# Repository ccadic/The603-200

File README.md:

# The603-200
A modern opensource watch in a vintage shell
https://hackaday.io/project/181159-the-603-200-watch
©2021 – Morpheans.com – pcadic@gmail.com 

**Description of the product**
The 603-200 is the first watch of a planed line of watches based on the same concept which is inspired by the Japanese TokyoFlash® brand (www.tokyoflash.com). We want to push the concept to a fully modern connected watch capable of establishing communication with your SmartPhone or any other IoT.
This watch is an open source device. The customers and makers have access to all the documentation

  •	Kicad-Pcb® files to make correction or updates
  •	Arduino IDE Sketches available from www.github.com to update or modify the watch’s behaviour 
  •	Python code available from www.github.com to update or modify the watch’s behaviour. You get access to hundreds of ESP32 code coming from the makers community.
  •	Technical documentation to create new top side displays (sister boatrd) and design add-ons
  •	3D files for CNC and 3D printers for those willing to create enclosure/shells in various material

**What the watch can do :**
The 603-200 Morphwatch® has been mainly design to produce exciting visual effects with its collertion of  192 leds. There are 4 circles of 603 size format SMD color leds. 

  •	1 external circle of 60 WHITE 603 leds for the seconds
  •	2 intermediate circles of PURPLE 603 Leds for the minutes
  •	1 internal circle of YELLOW 603 Leds for the hours

Each LED can be programmed independently with I2C libraries or through PYTHON Script. The user can be very creative with visual effects.  

Now the visual effects put aside, the watch has much more to offer because it has a powerfull Espressif® ESP32 PICO D4 chip. Therefore, it is a complete connected modern watch which is capable of interaction with your smartphone through Bluetooth. Using your phone you can use the watch to communicate into a private MESH wireless digital network. You can ask your watch to vibrate when your phone if away (with Bluetooth) or very far away (with WIFI).  

With 4 buttons, you can design your watch to trigger a relay, send an emergency email, send a vibration information to another watch  and more….

With MESH ESPNow protocol, each watch can talk to another, sometimes over hundreds of meters : you can build your private long range messenging system outside cellular networks...
You can switch your watch to be an access point, a web server so any one can connect to grab information (a watch business card concept…)

**And of course, you have guessed already, this watch can tell you the time ! 
**

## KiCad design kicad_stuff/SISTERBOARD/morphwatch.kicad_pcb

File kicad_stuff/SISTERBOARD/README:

Version 0.8
www.morpheans.com
Still under pressure and dev

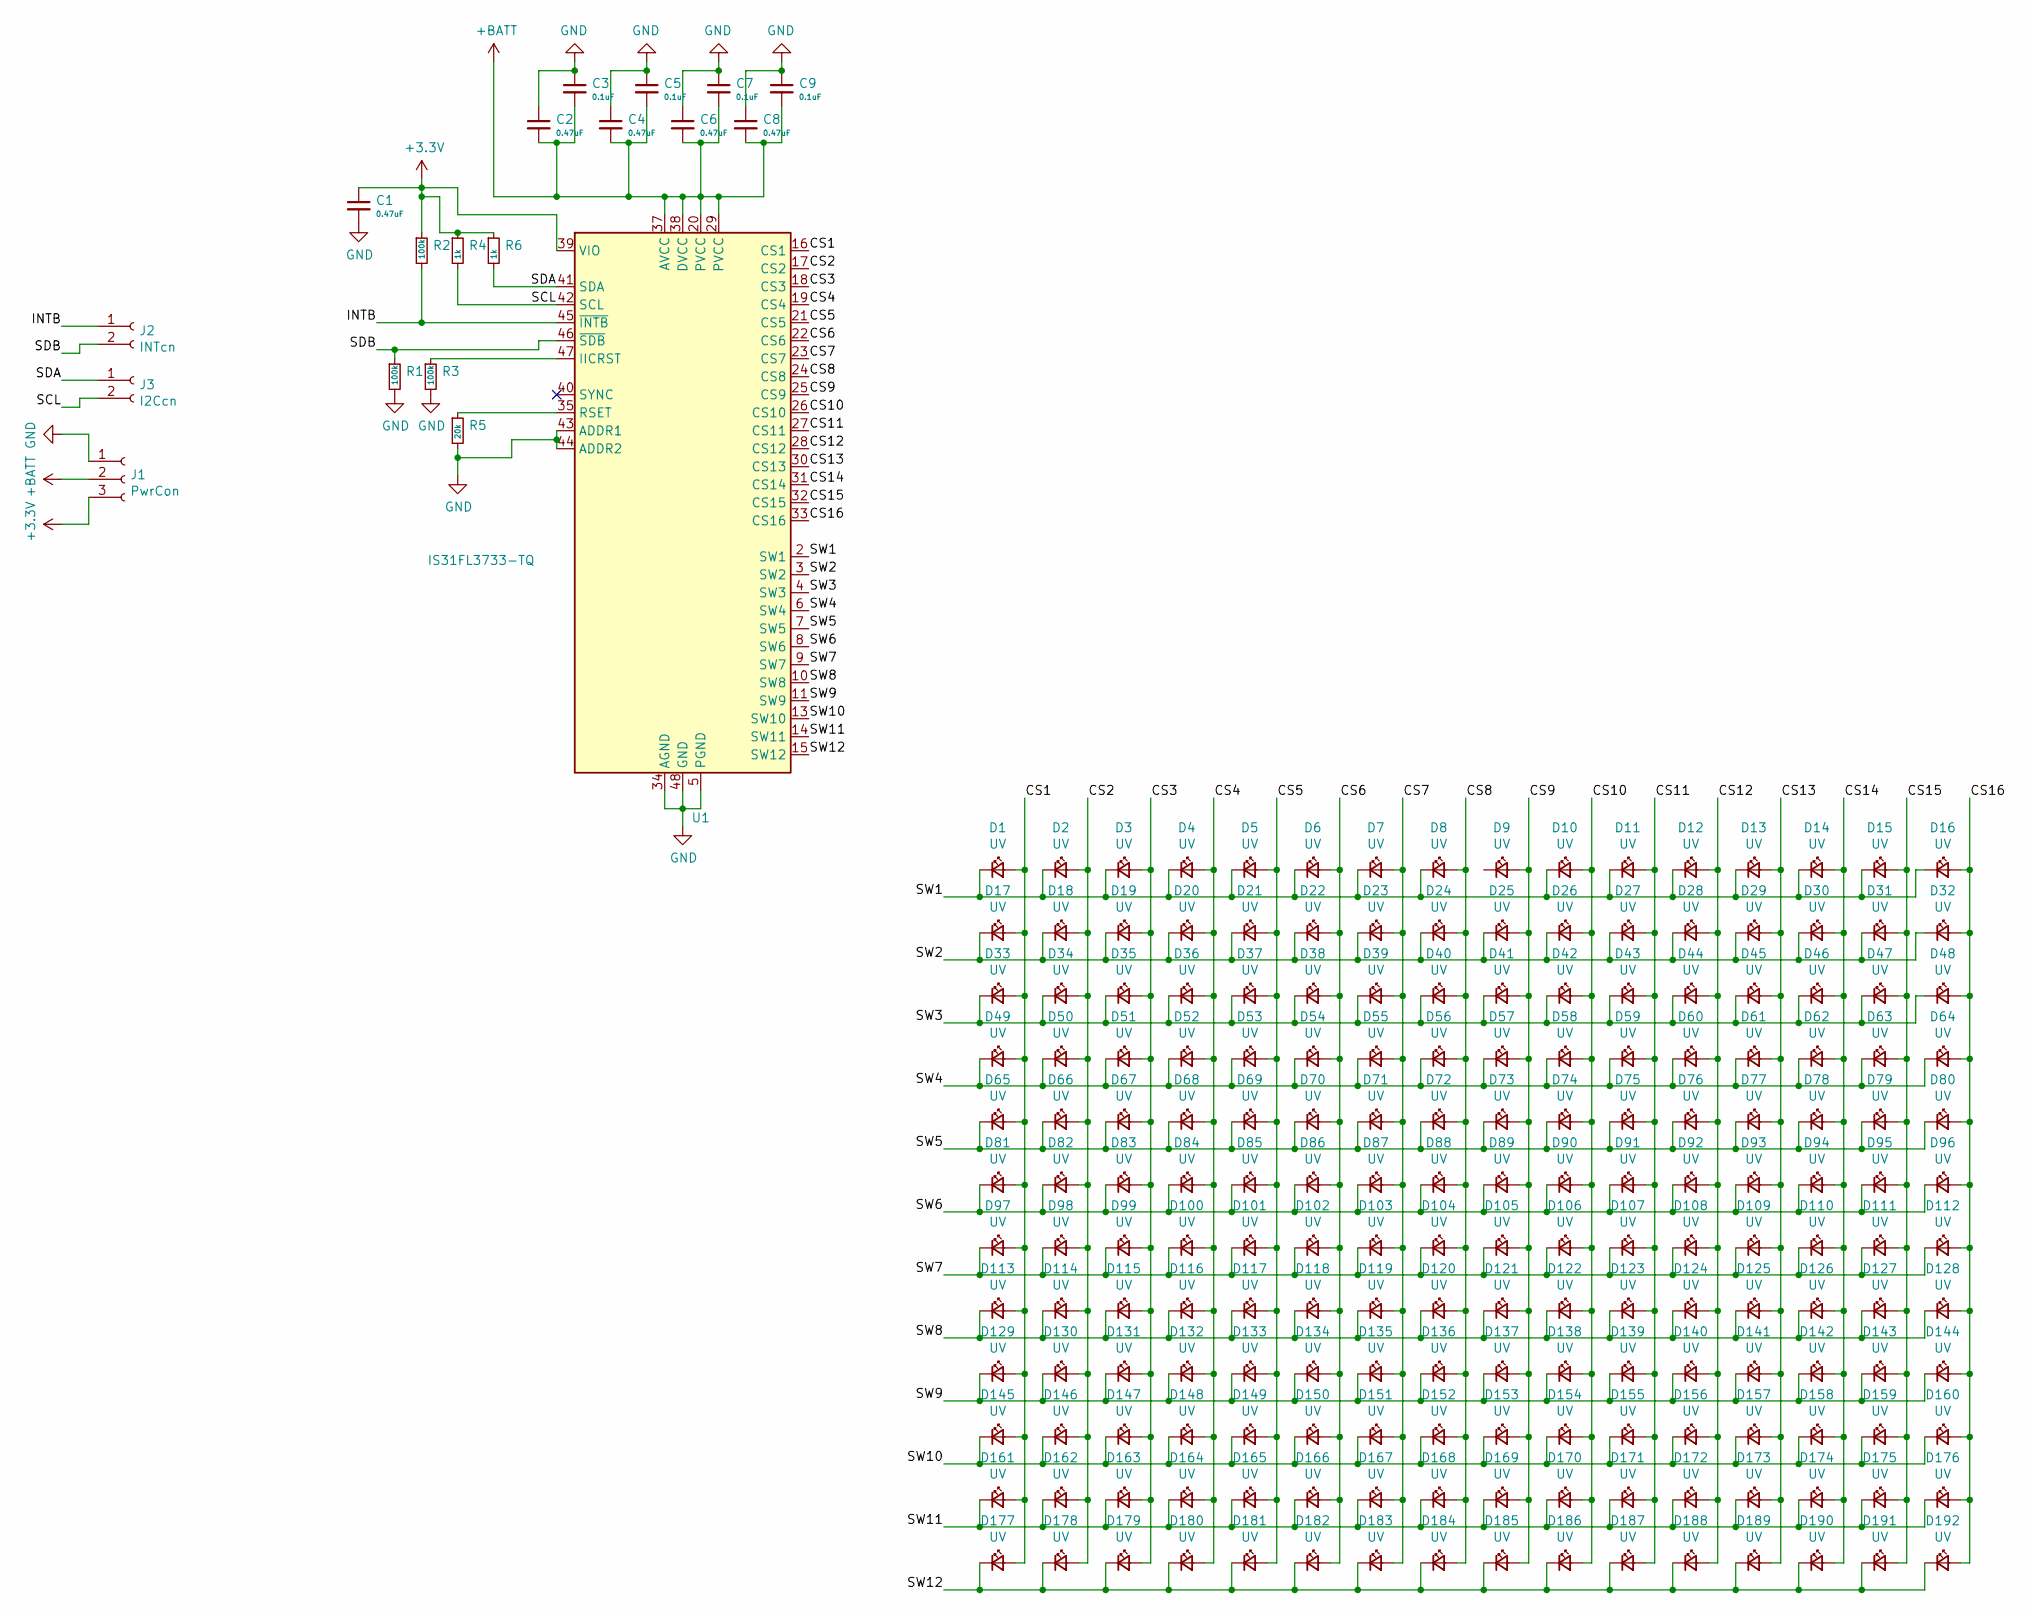
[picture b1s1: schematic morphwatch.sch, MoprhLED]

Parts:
C1, C2, C4, C6, C8: 0.47uF; C_0603_1608Metric_Pad1.08x0.95mm_HandSolder
C3, C5, C7, C9: 0.1uF; C_0603_1608Metric_Pad1.08x0.95mm_HandSolder
D1, D2, D3, D4, D5, D6, D7, D8, D9, D10, D11, D12, D13, D14, D15, D16, D17, D18, D19, D20, D21, D22, D23, D24, D25, D26, D27, D28, D29, D30, D31, D32, D33, D34, D35, D36, D37, D38, D39, D40, D41, D42, D43, D44, D45, D46, D47, D48, D49, D50, D51, D52, D53, D54, D55, D56, D57, D58, D59, D60, D61, D62, D63, D64, D65, D66, D67, D68, D69, D70, D71, D72, D73, D74, D75, D76, D77, D78, D79, D80, D81, D82, D83, D84, D85, D86, D87, D88, D89, D90, D91, D92, D93, D94, D95, D96, D97, D98, D99, D100, D101, D102, D103, D104, D105, D106, D107, D108, D109, D110, D111, D112, D113, D114, D115, D116, D117, D118, D119, D120, D121, D122, D123, D124, D125, D126, D127, D128, D129, D130, D131, D132, D133, D134, D135, D136, D137, D138, D139, D140, D141, D142, D143, D144, D145, D146, D147, D148, D149, D150, D151, D152, D153, D154, D155, D156, D157, D158, D159, D160, D161, D162, D163, D164, D165, D166, D167, D168, D169, D170, D171, D172, D173, D174, D175, D176, D177, D178, D179, D180, D181, D182, D183, D184, D185, D186, D187, D188, D189, D190, D191, D192: UV; LED_0603_1608Metric
J1: PwrCon; PinHeader_1x03_P1.27mm_Vertical
J2: INTcn; PinHeader_1x02_P1.27mm_Vertical
J3: I2Ccn; PinHeader_1x02_P1.27mm_Vertical
R1, R2, R3: 100k; R_0603_1608Metric_Pad0.98x0.95mm_HandSolder
R4, R6: 1k; R_0603_1608Metric_Pad0.98x0.95mm_HandSolder
R5: 20k; R_0603_1608Metric_Pad0.98x0.95mm_HandSolder
U1: IS31FL3733-TQ; TQFP-48-1EP_7x7mm_P0.5mm_EP3.5x3.5mm

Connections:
+3V3: C1.1, J1.3, R2.1, R4.1, R6.1, U1.39 (VIO)
+BATT: C2.2, C3.2, C4.2, C5.2, C6.2, C7.2, C8.2, C9.2, J1.2, U1.20 (PVCC), U1.29 (PVCC), U1.37 (AVCC), U1.38 (DVCC)
/CS1: D1.2 (A), D17.2 (A), D33.2 (A), D49.2 (A), D65.2 (A), D81.2 (A), D97.2 (A), D113.2 (A), D129.2 (A), D145.2 (A), D161.2 (A), D177.2 (A), U1.16 (CS1)
/CS2: D2.2 (A), D18.2 (A), D34.2 (A), D50.2 (A), D66.2 (A), D82.2 (A), D98.2 (A), D114.2 (A), D130.2 (A), D146.2 (A), D162.2 (A), D178.2 (A), U1.17 (CS2)
/CS3: D3.2 (A), D19.2 (A), D35.2 (A), D51.2 (A), D67.2 (A), D83.2 (A), D99.2 (A), D115.2 (A), D131.2 (A), D147.2 (A), D163.2 (A), D179.2 (A), U1.18 (CS3)
/CS4: D4.2 (A), D20.2 (A), D36.2 (A), D52.2 (A), D68.2 (A), D84.2 (A), D100.2 (A), D116.2 (A), D132.2 (A), D148.2 (A), D164.2 (A), D180.2 (A), U1.19 (CS4)
/CS5: D5.2 (A), D21.2 (A), D37.2 (A), D53.2 (A), D69.2 (A), D85.2 (A), D101.2 (A), D117.2 (A), D133.2 (A), D149.2 (A), D165.2 (A), D181.2 (A), U1.21 (CS5)
/CS6: D6.2 (A), D22.2 (A), D38.2 (A), D54.2 (A), D70.2 (A), D86.2 (A), D102.2 (A), D118.2 (A), D134.2 (A), D150.2 (A), D166.2 (A), D182.2 (A), U1.22 (CS6)
/CS7: D7.2 (A), D23.2 (A), D39.2 (A), D55.2 (A), D71.2 (A), D87.2 (A), D103.2 (A), D119.2 (A), D135.2 (A), D151.2 (A), D167.2 (A), D183.2 (A), U1.23 (CS7)
/CS8: D8.2 (A), D24.2 (A), D40.2 (A), D56.2 (A), D72.2 (A), D88.2 (A), D104.2 (A), D120.2 (A), D136.2 (A), D152.2 (A), D168.2 (A), D184.2 (A), U1.24 (CS8)
/CS9: D9.2 (A), D25.2 (A), D41.2 (A), D57.2 (A), D73.2 (A), D89.2 (A), D105.2 (A), D121.2 (A), D137.2 (A), D153.2 (A), D169.2 (A), D185.2 (A), U1.25 (CS9)
/CS10: D10.2 (A), D26.2 (A), D42.2 (A), D58.2 (A), D74.2 (A), D90.2 (A), D106.2 (A), D122.2 (A), D138.2 (A), D154.2 (A), D170.2 (A), D186.2 (A), U1.26 (CS10)
/CS11: D11.2 (A), D27.2 (A), D43.2 (A), D59.2 (A), D75.2 (A), D91.2 (A), D107.2 (A), D123.2 (A), D139.2 (A), D155.2 (A), D171.2 (A), D187.2 (A), U1.27 (CS11)
/CS12: D12.2 (A), D28.2 (A), D44.2 (A), D60.2 (A), D76.2 (A), D92.2 (A), D108.2 (A), D124.2 (A), D140.2 (A), D156.2 (A), D172.2 (A), D188.2 (A), U1.28 (CS12)
/CS13: D13.2 (A), D29.2 (A), D45.2 (A), D61.2 (A), D77.2 (A), D93.2 (A), D109.2 (A), D125.2 (A), D141.2 (A), D157.2 (A), D173.2 (A), D189.2 (A), U1.30 (CS13)
/CS14: D14.2 (A), D30.2 (A), D46.2 (A), D62.2 (A), D78.2 (A), D94.2 (A), D110.2 (A), D126.2 (A), D142.2 (A), D158.2 (A), D174.2 (A), D190.2 (A), U1.31 (CS14)
/CS15: D15.2 (A), D31.2 (A), D47.2 (A), D63.2 (A), D79.2 (A), D95.2 (A), D111.2 (A), D127.2 (A), D143.2 (A), D159.2 (A), D175.2 (A), D191.2 (A), U1.32 (CS15)
/CS16: D16.2 (A), D32.2 (A), D48.2 (A), D64.2 (A), D80.2 (A), D96.2 (A), D112.2 (A), D128.2 (A), D144.2 (A), D160.2 (A), D176.2 (A), D192.2 (A), U1.33 (CS16)
/INTB: J2.1, R2.2, U1.45 (~INTB)
/SCL: J3.2, R4.2, U1.42 (SCL)
/SDA: J3.1, R6.2, U1.41 (SDA)
/SDB: J2.2, R1.1, U1.46 (~SDB)
/SW1: D1.1 (K), D2.1 (K), D3.1 (K), D4.1 (K), D5.1 (K), D6.1 (K), D7.1 (K), D8.1 (K), D10.1 (K), D11.1 (K), D12.1 (K), D13.1 (K), D14.1 (K), D15.1 (K), D16.1 (K), U1.2 (SW1)
/SW2: D17.1 (K), D18.1 (K), D19.1 (K), D20.1 (K), D21.1 (K), D22.1 (K), D23.1 (K), D24.1 (K), D25.1 (K), D26.1 (K), D27.1 (K), D28.1 (K), D29.1 (K), D30.1 (K), D31.1 (K), D32.1 (K), U1.3 (SW2)
/SW3: D33.1 (K), D34.1 (K), D35.1 (K), D36.1 (K), D37.1 (K), D38.1 (K), D39.1 (K), D40.1 (K), D41.1 (K), D42.1 (K), D43.1 (K), D44.1 (K), D45.1 (K), D46.1 (K), D47.1 (K), D48.1 (K), U1.4 (SW3)
/SW4: D49.1 (K), D50.1 (K), D51.1 (K), D52.1 (K), D53.1 (K), D54.1 (K), D55.1 (K), D56.1 (K), D57.1 (K), D58.1 (K), D59.1 (K), D60.1 (K), D61.1 (K), D62.1 (K), D63.1 (K), D64.1 (K), U1.6 (SW4)
/SW5: D65.1 (K), D66.1 (K), D67.1 (K), D68.1 (K), D69.1 (K), D70.1 (K), D71.1 (K), D72.1 (K), D73.1 (K), D74.1 (K), D75.1 (K), D76.1 (K), D77.1 (K), D78.1 (K), D79.1 (K), D80.1 (K), U1.7 (SW5)
/SW6: D81.1 (K), D82.1 (K), D83.1 (K), D84.1 (K), D85.1 (K), D86.1 (K), D87.1 (K), D88.1 (K), D89.1 (K), D90.1 (K), D91.1 (K), D92.1 (K), D93.1 (K), D94.1 (K), D95.1 (K), D96.1 (K), U1.8 (SW6)
/SW7: D97.1 (K), D98.1 (K), D99.1 (K), D100.1 (K), D101.1 (K), D102.1 (K), D103.1 (K), D104.1 (K), D105.1 (K), D106.1 (K), D107.1 (K), D108.1 (K), D109.1 (K), D110.1 (K), D111.1 (K), D112.1 (K), U1.9 (SW7)
/SW8: D113.1 (K), D114.1 (K), D115.1 (K), D116.1 (K), D117.1 (K), D118.1 (K), D119.1 (K), D120.1 (K), D121.1 (K), D122.1 (K), D123.1 (K), D124.1 (K), D125.1 (K), D126.1 (K), D127.1 (K), D128.1 (K), U1.10 (SW8)
/SW9: D129.1 (K), D130.1 (K), D131.1 (K), D132.1 (K), D133.1 (K), D134.1 (K), D135.1 (K), D136.1 (K), D137.1 (K), D138.1 (K), D139.1 (K), D140.1 (K), D141.1 (K), D142.1 (K), D143.1 (K), D144.1 (K), U1.11 (SW9)
/SW10: D145.1 (K), D146.1 (K), D147.1 (K), D148.1 (K), D149.1 (K), D150.1 (K), D151.1 (K), D152.1 (K), D153.1 (K), D154.1 (K), D155.1 (K), D156.1 (K), D157.1 (K), D158.1 (K), D159.1 (K), D160.1 (K), U1.13 (SW10)
/SW11: D161.1 (K), D162.1 (K), D163.1 (K), D164.1 (K), D165.1 (K), D166.1 (K), D167.1 (K), D168.1 (K), D169.1 (K), D170.1 (K), D171.1 (K), D172.1 (K), D173.1 (K), D174.1 (K), D175.1 (K), D176.1 (K), U1.14 (SW11)
/SW12: D177.1 (K), D178.1 (K), D179.1 (K), D180.1 (K), D181.1 (K), D182.1 (K), D183.1 (K), D184.1 (K), D185.1 (K), D186.1 (K), D187.1 (K), D188.1 (K), D189.1 (K), D190.1 (K), D191.1 (K), D192.1 (K), U1.15 (SW12)
GND: C1.2, C2.1, C3.1, C4.1, C5.1, C6.1, C7.1, C8.1, C9.1, J1.1, R1.2, R3.2, R5.2, U1.5 (PGND), U1.12 (PGND), U1.34 (AGND), U1.43 (ADDR1), U1.44 (ADDR2), U1.48 (GND), U1.49 (GND)
unnamed: R3.1, U1.47 (IICRST)
unnamed: R5.1, U1.35 (RSET)

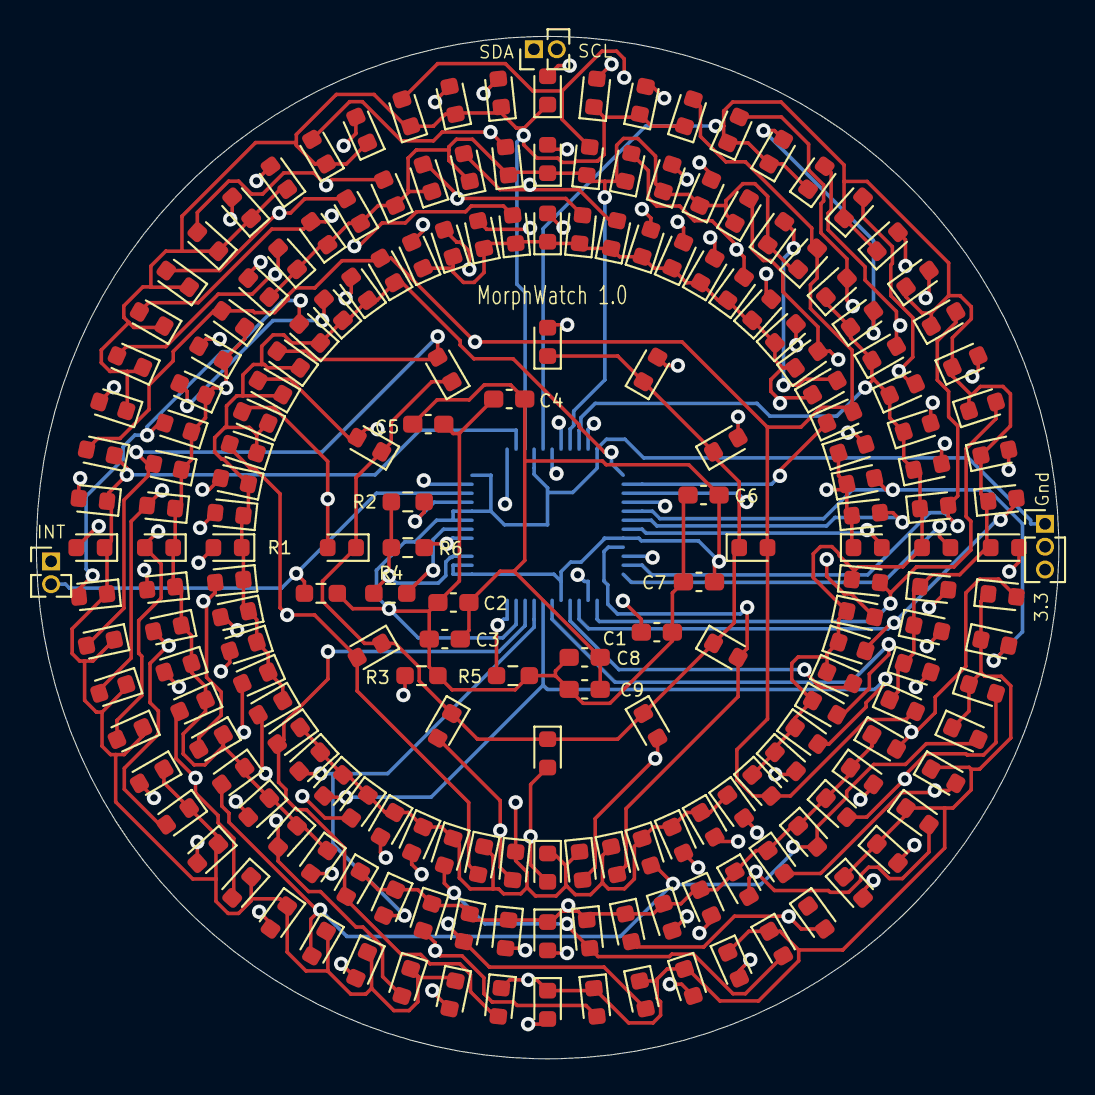
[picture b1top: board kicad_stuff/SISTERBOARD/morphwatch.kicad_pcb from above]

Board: 4 copper layers, 56.8 x 56.8 mm, 211 parts (1 on the bottom side), 37 nets.

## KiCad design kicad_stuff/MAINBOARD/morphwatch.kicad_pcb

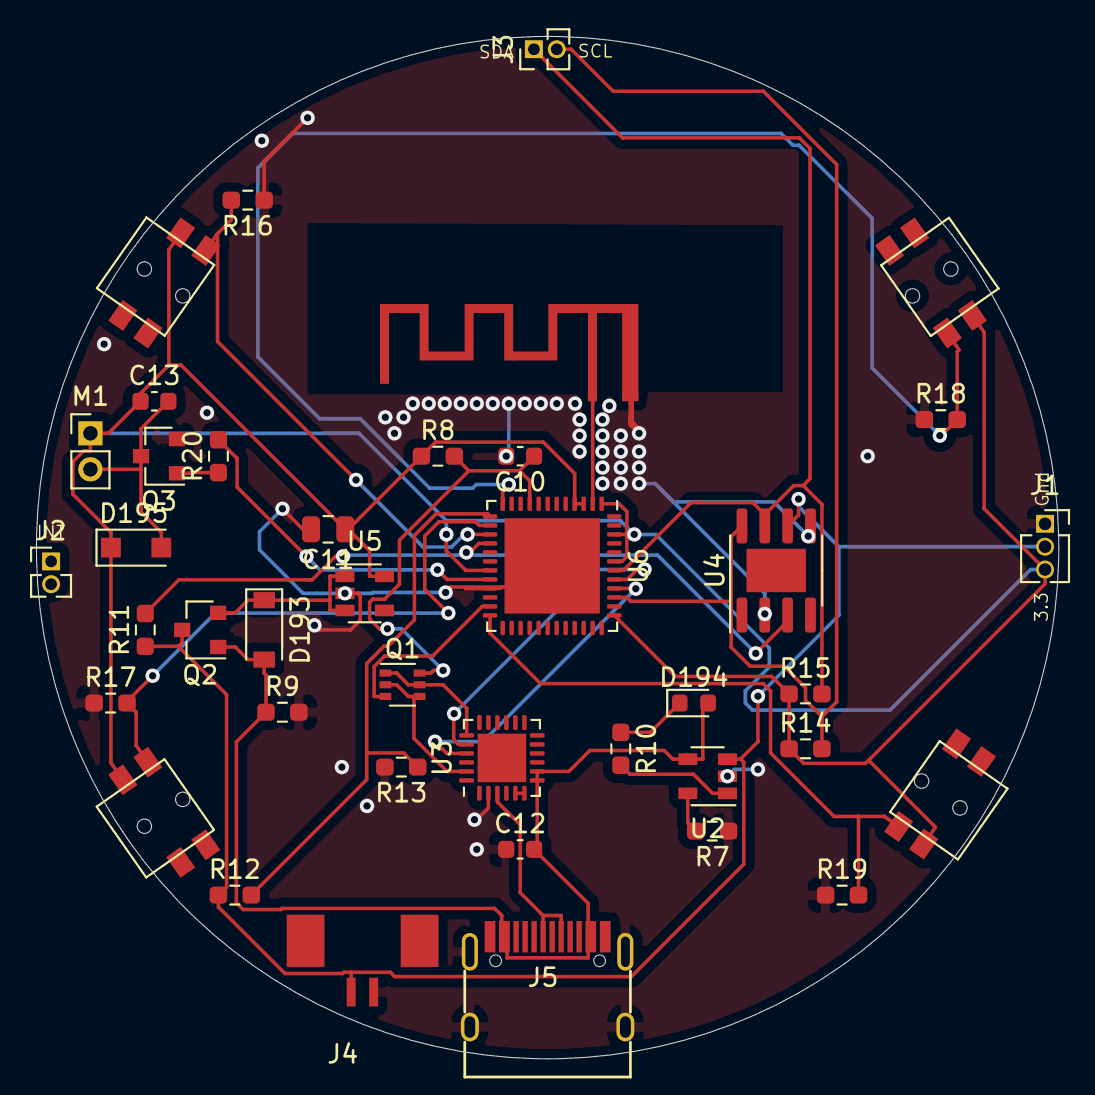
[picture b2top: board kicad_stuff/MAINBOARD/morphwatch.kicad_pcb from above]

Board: 2 copper layers, 56.8 x 56.8 mm, 40 parts (0 on the bottom side), 28 nets.

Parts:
AE1: SWRA117D
C10, C12, C13: 100nF; C_0603_1608Metric
C11: 4.7uF/50V; C_0805_2012Metric
D193: MBR0530; D_SOD-123
D194: LED; D_0603_1608Metric
D195: 1N4001; D_SOD-123F
J1: PwrCon; PinSocket_1x03_P1.27mm_Vertical
J2: INTcn; PinHeader_1x02_P1.27mm_Vertical
J3: I2Ccn; PinHeader_1x02_P1.27mm_Vertical
J4: Battery; 1.25T-2PWT (Molex 532610271)
J5: USB_C_Receptacle; GT-USB-7010
M1: Vibration_Motor; PinHeader_1x02_P2.00mm_Vertical
Q1: UMH3N; SOT-363_SC-70-6
Q2: CJ2301; SOT-23
Q3: S8050; SOT-23
R7, R8, R9, R11, R16, R17, R18, R19: 10K; R_0603_1608Metric_Pad0.98x0.95mm_HandSolder
R10, R20: 1K; R_0603_1608Metric_Pad0.98x0.95mm_HandSolder
R12, R13: 100K; R_0603_1608Metric_Pad0.98x0.95mm_HandSolder
R14, R15: 4.7K; R_0603_1608Metric_Pad0.98x0.95mm_HandSolder
SW1, SW2, SW3, SW4: BTN; K2-1114SA-A4SW-06
U2: TP4054; SOT-23-5
U3: CP2104; QFN-24-1EP_4x4mm_P0.5mm_EP2.7x2.7mm
U4: DS3231MZ; SOIC-8-1EP_3.9x4.9mm_P1.27mm_EP2.41x3.3mm
U5: ME6211C33M5G-N; SOT-23-5
U6: ESP32-PICO-D4; QFN-48-1EP_7x7mm_P0.5mm_EP5.3x5.3mm

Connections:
+3V3: C11.1, C13.1, D195.1, J1.3, M1.1, R8.1, R14.1, R15.1, SW1.1, SW2.1, SW3.1, SW4.1, U5.5, U6.1, U6.3, U6.4, U6.19, U6.37, U6.43, U6.46
+BATT: J1.2, J4.1, Q2.3, R11.1, R12.1, U2.3, U4.6
/D+: J5.A6, J5.B6, U3.3
ADC: R12.2, R13.1, U6.13
BTN_1: R16.2, SW1.2, U6.15
BTN_2: R17.2, SW2.2, U6.14
BTN_3: R18.2, SW3.2, U6.12
BTN_4: R19.2, SW4.2, U6.24
DTR: Q1.2, Q1.4, U3.23
EN: C10.1, Q1.6, R8.2, U6.9
GND: AE1.2, C10.2, C11.2, C12.1, J1.1, J4.2, J5.A1, J5.A12, J5.B1, J5.B12, J5.S1, Q3.2, R7.1, R9.2, R13.2, R16.1, R17.1, R18.1, R19.1, U2.2, U3.2, U4.2, U4.5, U5.2, U6.21, U6.49
GPIO0: Q1.3, U6.23
unnamed: AE1.1, U6.2
unnamed: C13.2, D195.2, M1.2, Q3.3
unnamed: D193.1, Q2.2, U5.1, U5.3
unnamed: D194.1, R10.1
unnamed: Q3.1, R20.1
unnamed: R7.2, U2.5
unnamed: R10.2, U2.1
unnamed: U3.5, U3.6
RTC_INT: R11.2, U4.3, U6.16
RTS: Q1.1, Q1.5, U3.19
RX: U3.21, U6.40
SCL: J3.2, R14.2, U4.8, U6.39
SDA: J3.1, R15.2, U4.7, U6.42
TX: U3.20, U6.41
VBUS: C12.2, D193.2, D194.2, J5.A4, J5.A9, J5.B4, J5.B9, Q2.1, R9.1, U2.4, U3.7, U3.8
VIB_PWM: R20.2, U6.20

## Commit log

2021-08-19 Create LICENCE
